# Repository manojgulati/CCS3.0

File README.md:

# CCS3.0
UW Contactless Circuit Level Current Sensor

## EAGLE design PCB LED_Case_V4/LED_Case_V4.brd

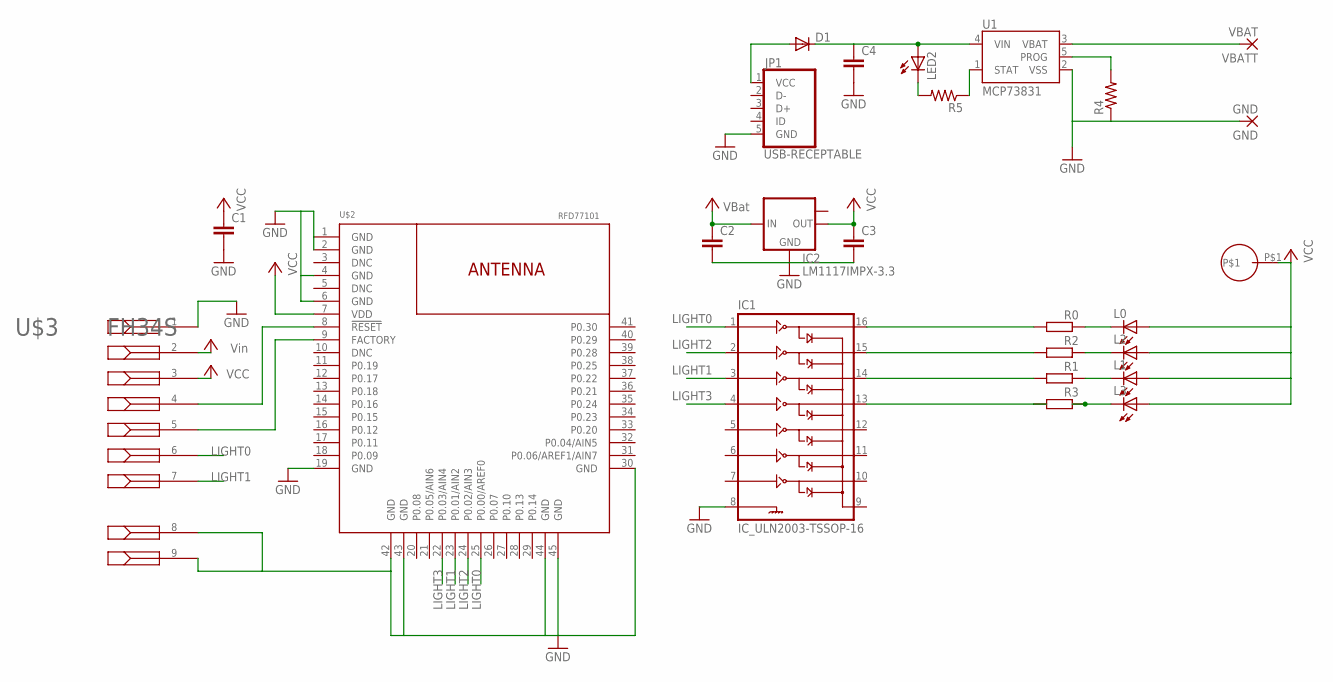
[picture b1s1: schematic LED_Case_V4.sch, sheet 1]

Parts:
C1, C2, C3, C4: CC0603; C0603
D1: DIODE-DO214AC; DO214AC
GND: GND; SMD1,27-2,54
IC1: IC_ULN2003-TSSOP-16; TSSOP-16
IC2: LM1117IMPX-3.3; SOT223
JP1: USB-RECEPTABLE; FCI-10103594-0001LF
L0, L1, L2: LEDCHIP-LED0805; CHIP-LED0805
L3: LEDP-LCC-2-SMT; P-LCC-2-WIDE
LED2: LED_ESML0603; LED_SML0603
R0, R1, R2, R3: RR0603; R0603
R4, R5: R-US_R0603; R0603
U1: MCP73831; SOT23-5
U$1: RING_CONNECTOR; RING
U$2: RFD77101
U$3: FH34S; CONN7_1X7_DR_FFC
VBATT: VBAT; SMD1,27-2,54

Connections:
GND: C1.2, C2.2, C3.2, C4.2, GND.1, IC1.8 (GND), IC2.1 (GND), JP1.5 (GND), R4.1, U1.2 (VSS), U$2.1 (GND), U$2.2 (GND), U$2.4 (GND), U$2.6 (GND), U$2.19 (GND), U$2.30 (GND), U$2.42 (GND), U$2.43 (GND), U$2.44 (GND), U$2.45 (GND), U$3.1, U$3.8, U$3.9
LIGHT0: IC1.1 (1B), U$2.25 (P0.00/AREF0), U$3.6
LIGHT1: IC1.3 (3B), U$2.23 (P0.01/AIN2), U$3.7
LIGHT2: IC1.2 (2B), U$2.24 (P0.02/AIN3)
LIGHT3: IC1.4 (4B), U$2.22 (P0.03/AIN4)
unnamed: L0.C, R0.1
unnamed: L3.C, R3.1
unnamed: L2.C, R2.1
unnamed: U$2.9 (FACTORY), U$3.5
unnamed: L1.C, R1.1
unnamed: IC1.13 (4C), R3.2
unnamed: IC1.16 (1C), R0.2
unnamed: R4.2, U1.5 (PROG)
unnamed: IC1.15 (2C), R2.2
unnamed: D1.A, JP1.1 (VCC)
unnamed: IC1.14 (3C), R1.2
unnamed: LED2.C, R5.2
unnamed: R5.1, U1.1 (STAT)
RESET: U$2.8 (!RESET!), U$3.4
VBAT: C2.1, IC2.3 (IN), U1.3 (VBAT), VBATT.1
VCC: C1.1, C3.1, IC2.2 (OUT), L0.A, L1.A, L2.A, L3.A, U$1.P$1, U$2.7 (VDD), U$3.3
VIN: C4.1, D1.C, LED2.A, U1.4 (VIN), U$3.2

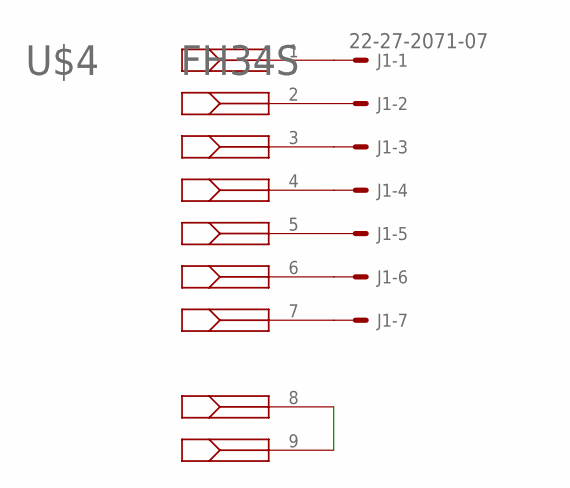
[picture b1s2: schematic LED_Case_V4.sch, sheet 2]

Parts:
J1: 22-27-2071-07; 6410-07
U$4: FH34S; CONN7_1X7_DR_FFC

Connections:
unnamed: J1.1, U$4.1
unnamed: J1.2, U$4.2
unnamed: J1.3, U$4.3
unnamed: J1.4, U$4.4
unnamed: J1.5, U$4.5
unnamed: J1.6, U$4.6
unnamed: J1.7, U$4.7
PROG: U$4.8, U$4.9

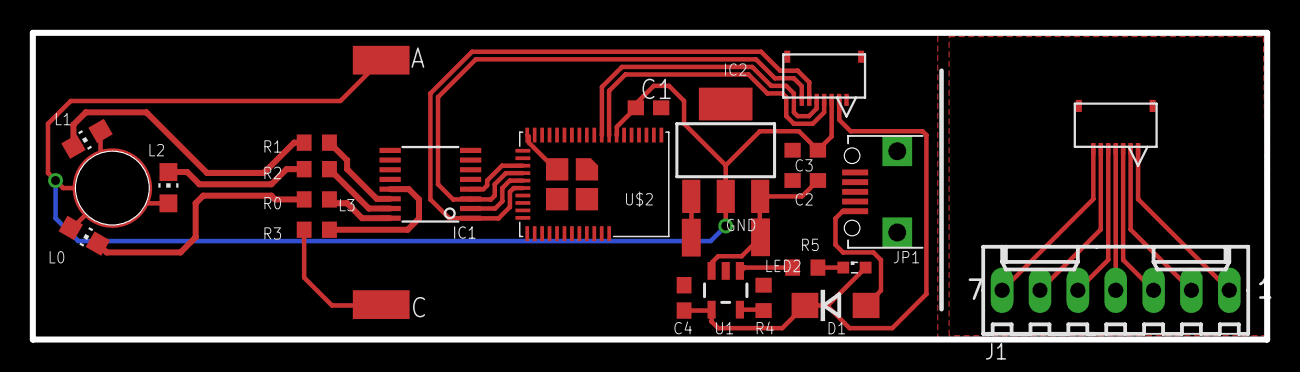
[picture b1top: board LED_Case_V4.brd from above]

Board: 2 copper layers, 82.8 x 20.6 mm, 27 parts (0 on the bottom side), 30 nets.

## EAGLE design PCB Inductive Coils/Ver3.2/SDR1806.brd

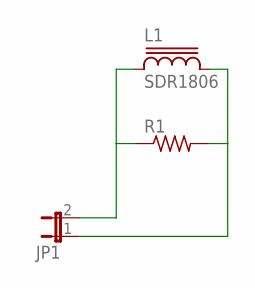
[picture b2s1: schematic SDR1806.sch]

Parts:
JP1: JP1E; JP1
L1: SDR1806
R1: R-US_R0603; R0603

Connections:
unnamed: JP1.2, L1.1, R1.1
unnamed: JP1.1, L1.2, R1.2

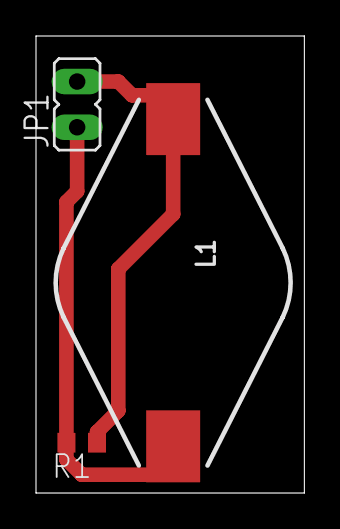
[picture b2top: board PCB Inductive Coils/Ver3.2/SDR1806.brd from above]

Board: 2 copper layers, 14.9 x 25.4 mm, 3 parts (0 on the bottom side), 2 nets.

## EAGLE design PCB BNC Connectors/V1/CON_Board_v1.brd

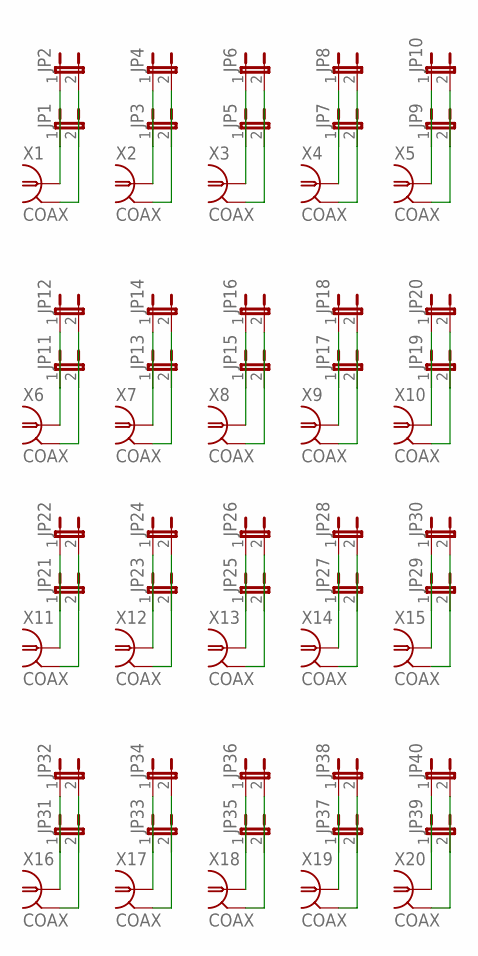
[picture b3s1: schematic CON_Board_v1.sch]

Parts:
JP1, JP2, JP3, JP4, JP5, JP6, JP7, JP8, JP9, JP10, JP11, JP12, JP13, JP14, JP15, JP16, JP17, JP18, JP19, JP20, JP21, JP22, JP23, JP24, JP25, JP26, JP27, JP28, JP29, JP30, JP31, JP32, JP33, JP34, JP35, JP36, JP37, JP38, JP39, JP40: JP1E; JP1
X1, X2, X3, X4, X5, X6, X7, X8, X9, X10, X11, X12, X13, X14, X15, X16, X17, X18, X19, X20: COAX; 31-5329

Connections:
unnamed: JP1.1, JP2.1, X1.1
unnamed: JP1.2, JP2.2, X1.2, X1.3 (2), X1.4 (2), X1.5 (2)
unnamed: JP3.1, JP4.1, X2.1
unnamed: JP3.2, JP4.2, X2.2, X2.3 (2), X2.4 (2), X2.5 (2)
unnamed: JP5.1, JP6.1, X3.1
unnamed: JP5.2, JP6.2, X3.2, X3.3 (2), X3.4 (2), X3.5 (2)
unnamed: JP7.1, JP8.1, X4.1
unnamed: JP7.2, JP8.2, X4.2, X4.3 (2), X4.4 (2), X4.5 (2)
unnamed: JP9.1, JP10.1, X5.1
unnamed: JP9.2, JP10.2, X5.2, X5.3 (2), X5.4 (2), X5.5 (2)
unnamed: JP11.1, JP12.1, X6.1
unnamed: JP11.2, JP12.2, X6.2, X6.3 (2), X6.4 (2), X6.5 (2)
unnamed: JP13.1, JP14.1, X7.1
unnamed: JP13.2, JP14.2, X7.2, X7.3 (2), X7.4 (2), X7.5 (2)
unnamed: JP15.1, JP16.1, X8.1
unnamed: JP15.2, JP16.2, X8.2, X8.3 (2), X8.4 (2), X8.5 (2)
unnamed: JP17.1, JP18.1, X9.1
unnamed: JP17.2, JP18.2, X9.2, X9.3 (2), X9.4 (2), X9.5 (2)
unnamed: JP19.1, JP20.1, X10.1
unnamed: JP19.2, JP20.2, X10.2, X10.3 (2), X10.4 (2), X10.5 (2)
unnamed: JP21.1, JP22.1, X11.1
unnamed: JP21.2, JP22.2, X11.2, X11.3 (2), X11.4 (2), X11.5 (2)
unnamed: JP23.1, JP24.1, X12.1
unnamed: JP23.2, JP24.2, X12.2, X12.3 (2), X12.4 (2), X12.5 (2)
unnamed: JP25.1, JP26.1, X13.1
unnamed: JP25.2, JP26.2, X13.2, X13.3 (2), X13.4 (2), X13.5 (2)
unnamed: JP27.1, JP28.1, X14.1
unnamed: JP27.2, JP28.2, X14.2, X14.3 (2), X14.4 (2), X14.5 (2)
unnamed: JP29.1, JP30.1, X15.1
unnamed: JP29.2, JP30.2, X15.2, X15.3 (2), X15.4 (2), X15.5 (2)
unnamed: JP31.1, JP32.1, X16.1
unnamed: JP31.2, JP32.2, X16.2, X16.3 (2), X16.4 (2), X16.5 (2)
unnamed: JP33.1, JP34.1, X17.1
unnamed: JP33.2, JP34.2, X17.2, X17.3 (2), X17.4 (2), X17.5 (2)
unnamed: JP35.1, JP36.1, X18.1
unnamed: JP35.2, JP36.2, X18.2, X18.3 (2), X18.4 (2), X18.5 (2)
unnamed: JP37.1, JP38.1, X19.1
unnamed: JP37.2, JP38.2, X19.2, X19.3 (2), X19.4 (2), X19.5 (2)
unnamed: JP39.1, JP40.1, X20.1
unnamed: JP39.2, JP40.2, X20.2, X20.3 (2), X20.4 (2), X20.5 (2)

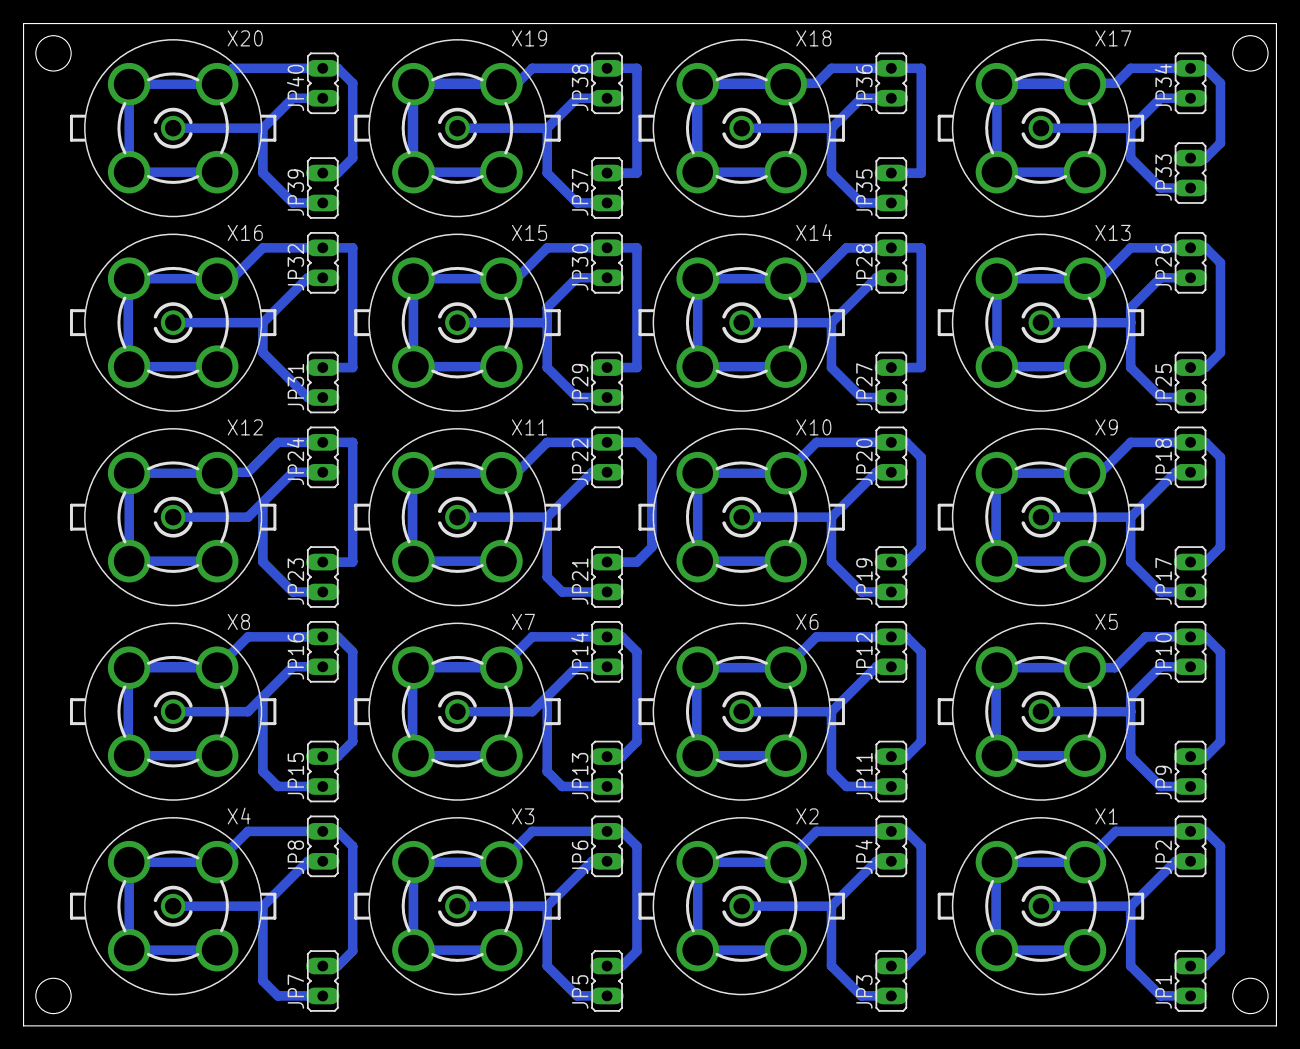
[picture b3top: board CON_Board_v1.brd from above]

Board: 2 copper layers, 106.3 x 85.1 mm, 60 parts (0 on the bottom side), 40 nets.

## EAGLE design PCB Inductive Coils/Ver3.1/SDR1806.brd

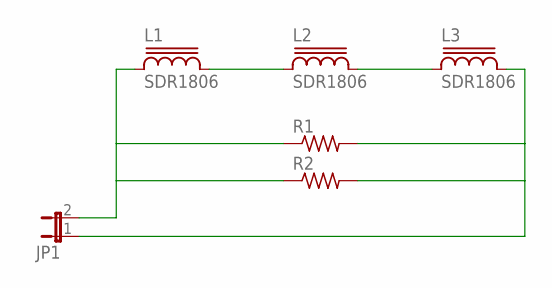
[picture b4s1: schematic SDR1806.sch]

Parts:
JP1: JP1E; JP1
L1, L2, L3: SDR1806
R1, R2: R-US_R0603; R0603

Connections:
unnamed: L1.2, L2.1
unnamed: L2.2, L3.1
unnamed: JP1.2, L1.1, R1.1, R2.1
unnamed: JP1.1, L3.2, R1.2, R2.2

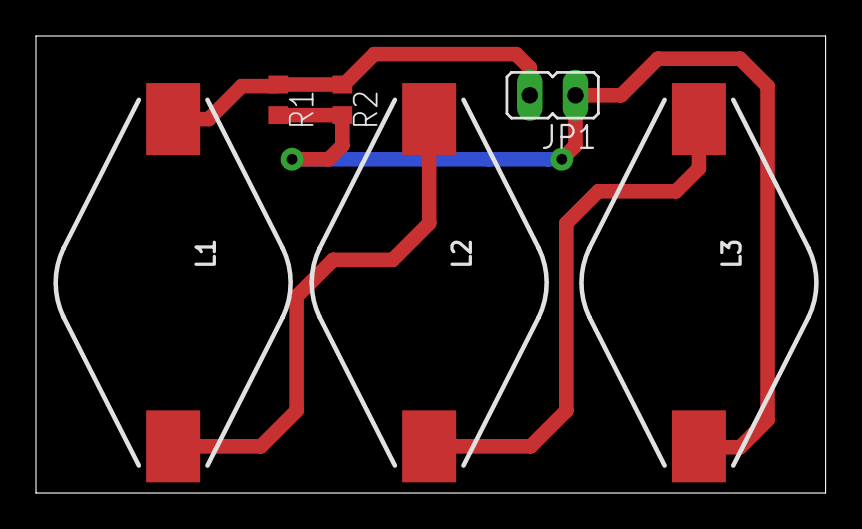
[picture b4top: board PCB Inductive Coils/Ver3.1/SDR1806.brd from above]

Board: 2 copper layers, 43.9 x 25.4 mm, 6 parts (0 on the bottom side), 4 nets.

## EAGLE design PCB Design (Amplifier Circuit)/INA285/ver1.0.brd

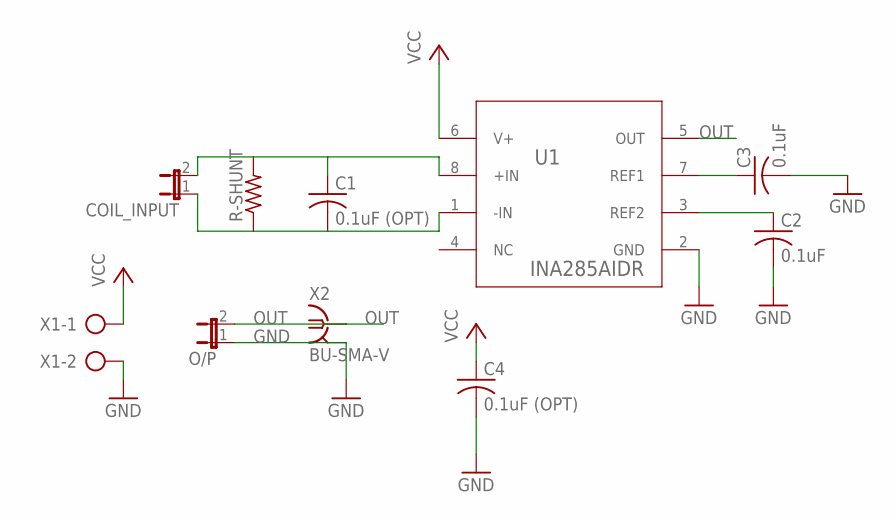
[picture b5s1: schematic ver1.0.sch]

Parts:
C1, C4: 0.1uF (OPT); C0603
C2, C3: 0.1uF; C0603
COIL_INPUT: JP1E; JP1
O/P: JP1E; JP1
R-SHUNT: R-US_R0603; R0603
U1: INA285AIDR; D0008A_M
X1: AK500/2
X2: BU-SMA-V

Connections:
GND: C2.2, C3.2, C4.2, O/P.1, U1.2 (GND), X1.2, X2.2, X2.3 (2), X2.4 (2), X2.5 (2)
unnamed: C2.1, U1.3 (REF2)
unnamed: C3.1, U1.7 (REF1)
unnamed: C1.1, COIL_INPUT.2, R-SHUNT.2, U1.8 (+IN)
unnamed: C1.2, COIL_INPUT.1, R-SHUNT.1, U1.1 (-IN)
OUT: O/P.2, U1.5 (OUT), X2.1
VCC: C4.1, U1.6 (V+), X1.1

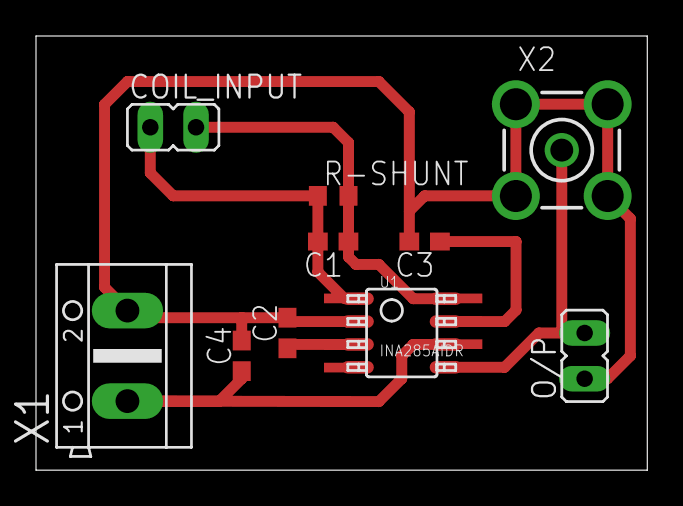
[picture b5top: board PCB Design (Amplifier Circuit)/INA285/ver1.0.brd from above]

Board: 2 copper layers, 34.0 x 24.1 mm, 10 parts (0 on the bottom side), 7 nets.

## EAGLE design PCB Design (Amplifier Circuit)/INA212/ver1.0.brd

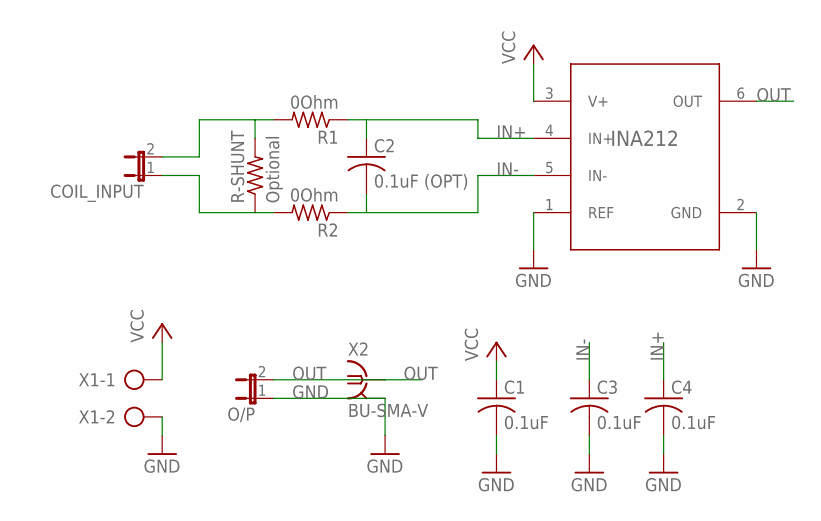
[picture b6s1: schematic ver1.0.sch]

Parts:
C1, C3, C4: 0.1uF; C0603
C2: 0.1uF (OPT); C0603
COIL_INPUT: JP1E; JP1
INA212: INA212AIDCKR; DCK0006A_M
O/P: JP1E; JP1
R1, R2: 0Ohm; R0603
R-SHUNT: Optional; R0603
X1: AK500/2
X2: BU-SMA-V

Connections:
GND: C1.2, C3.2, C4.2, INA212.1 (REF), INA212.2 (GND), O/P.1, X1.2, X2.2, X2.3 (2), X2.4 (2), X2.5 (2)
IN+: C2.1, C4.1, INA212.4 (IN+), R1.1
IN-: C2.2, C3.1, INA212.5 (IN-), R2.1
unnamed: COIL_INPUT.2, R1.2, R-SHUNT.2
unnamed: COIL_INPUT.1, R2.2, R-SHUNT.1
OUT: INA212.6 (OUT), O/P.2, X2.1
VCC: C1.1, INA212.3 (V+), X1.1

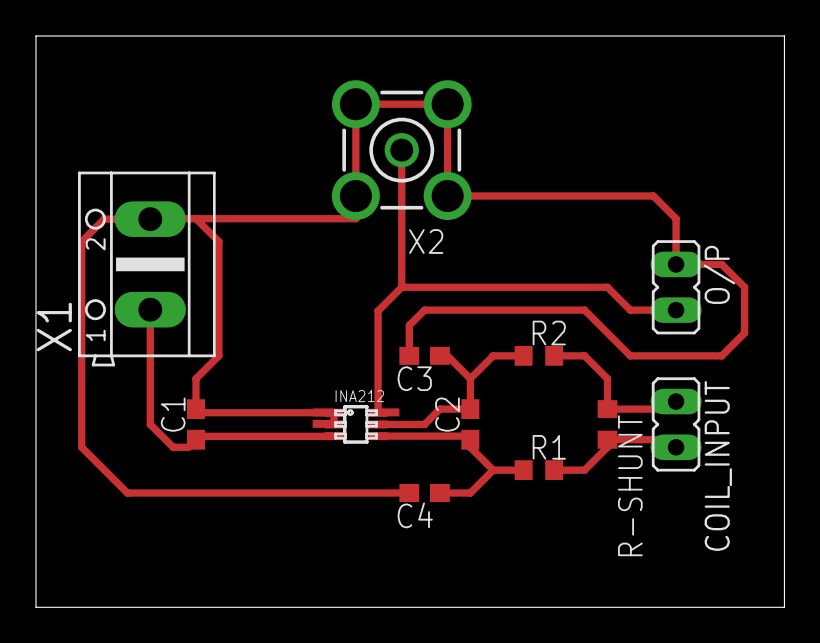
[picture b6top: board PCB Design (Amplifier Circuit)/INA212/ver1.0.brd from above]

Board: 2 copper layers, 41.6 x 31.7 mm, 12 parts (0 on the bottom side), 7 nets.

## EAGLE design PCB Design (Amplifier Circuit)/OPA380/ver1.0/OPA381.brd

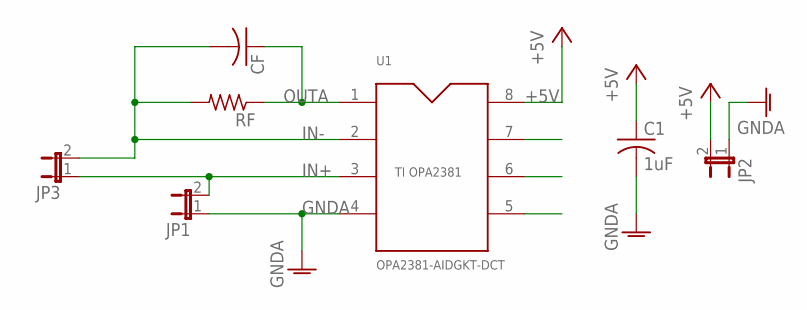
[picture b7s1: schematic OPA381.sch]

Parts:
C1: 1uF; C0603
CF: C-USC0603; C0603
JP1, JP2, JP3: JP1E; JP1
RF: R-US_R0603; R0603
U1: OPA2381-AIDGKT-DCT; SSOP8

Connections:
+5V: C1.1, JP2.2, U1.8
GNDA: C1.2, JP1.1, JP2.1, U1.4
IN+: JP1.2, JP3.1, U1.3
IN-: CF.2, JP3.2, RF.2, U1.2
OUTA: CF.1, RF.1, U1.1

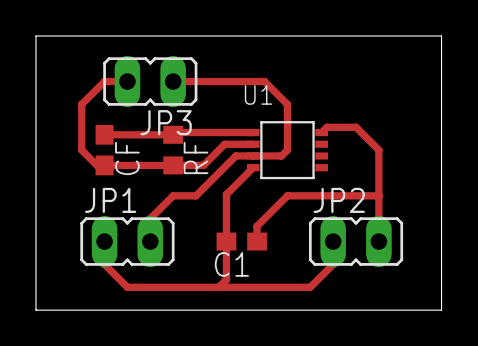
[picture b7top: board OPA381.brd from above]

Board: 2 copper layers, 22.5 x 15.2 mm, 7 parts (0 on the bottom side), 5 nets.

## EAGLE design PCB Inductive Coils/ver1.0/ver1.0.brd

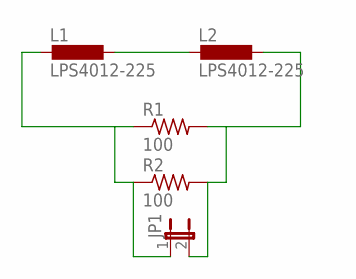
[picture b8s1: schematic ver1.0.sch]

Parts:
JP1: JP1E; JP1
L1, L2: LPS4012-225; MSS7341
R1, R2: 100; R0603

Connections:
unnamed: L1.P$2 (2), L2.P$1 (1)
unnamed: JP1.1, L1.P$1 (1), R1.1, R2.1
unnamed: JP1.2, L2.P$2 (2), R1.2, R2.2

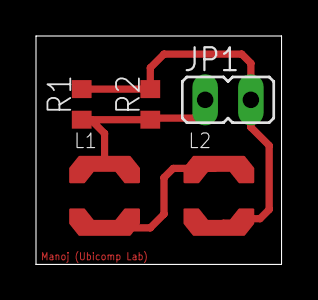
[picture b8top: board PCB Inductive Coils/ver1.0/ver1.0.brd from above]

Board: 2 copper layers, 13.6 x 12.7 mm, 5 parts (0 on the bottom side), 3 nets.

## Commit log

2016-03-25 backup of scripts and schematics
2016-03-27 rev2
2016-04-19 added scripts and instrumentation amplifier circuits
2016-05-23 updated source code and added realtime scripts
2016-05-23 added a script to compute angle of time series
2016-05-23 updated scripts
2016-05-29 updated scripts and removed junk
2016-06-14 added scripts and PCB files
2016-06-22 added some board files and some scripts
2016-07-27 added scripts to account for destructive interference
2016-08-03 added scripts for pilot deployments
2016-08-08 revised scripts
2016-10-23 added new scripts for post processing
2016-11-29 added post processing scripts
2016-12-22 Added scripts for scaling complex current to absolute current
2016-12-27 added current scaling function
2017-01-01 updated processing scripts for lab data
2017-02-09 updated scripts for Nordheim and Wilsonian APT

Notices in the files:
parts and their libraries:
RFDigital: © 2015 RF Digital Corporation
SparkFun-PowerIC: Licensing: Creative Commons ShareAlike 4.0 International - https://creativecommons.org/licenses/by-sa/4.0
